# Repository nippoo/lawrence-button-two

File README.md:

# Lawrence Button Two

This repository contains the STL files, KiCad design and Gerber files, and Arduino code used in building the Lawrence Button Two. Unlike the first button (a custom STM32-based audio player) the electronics are a simpler, through-hole-only design.

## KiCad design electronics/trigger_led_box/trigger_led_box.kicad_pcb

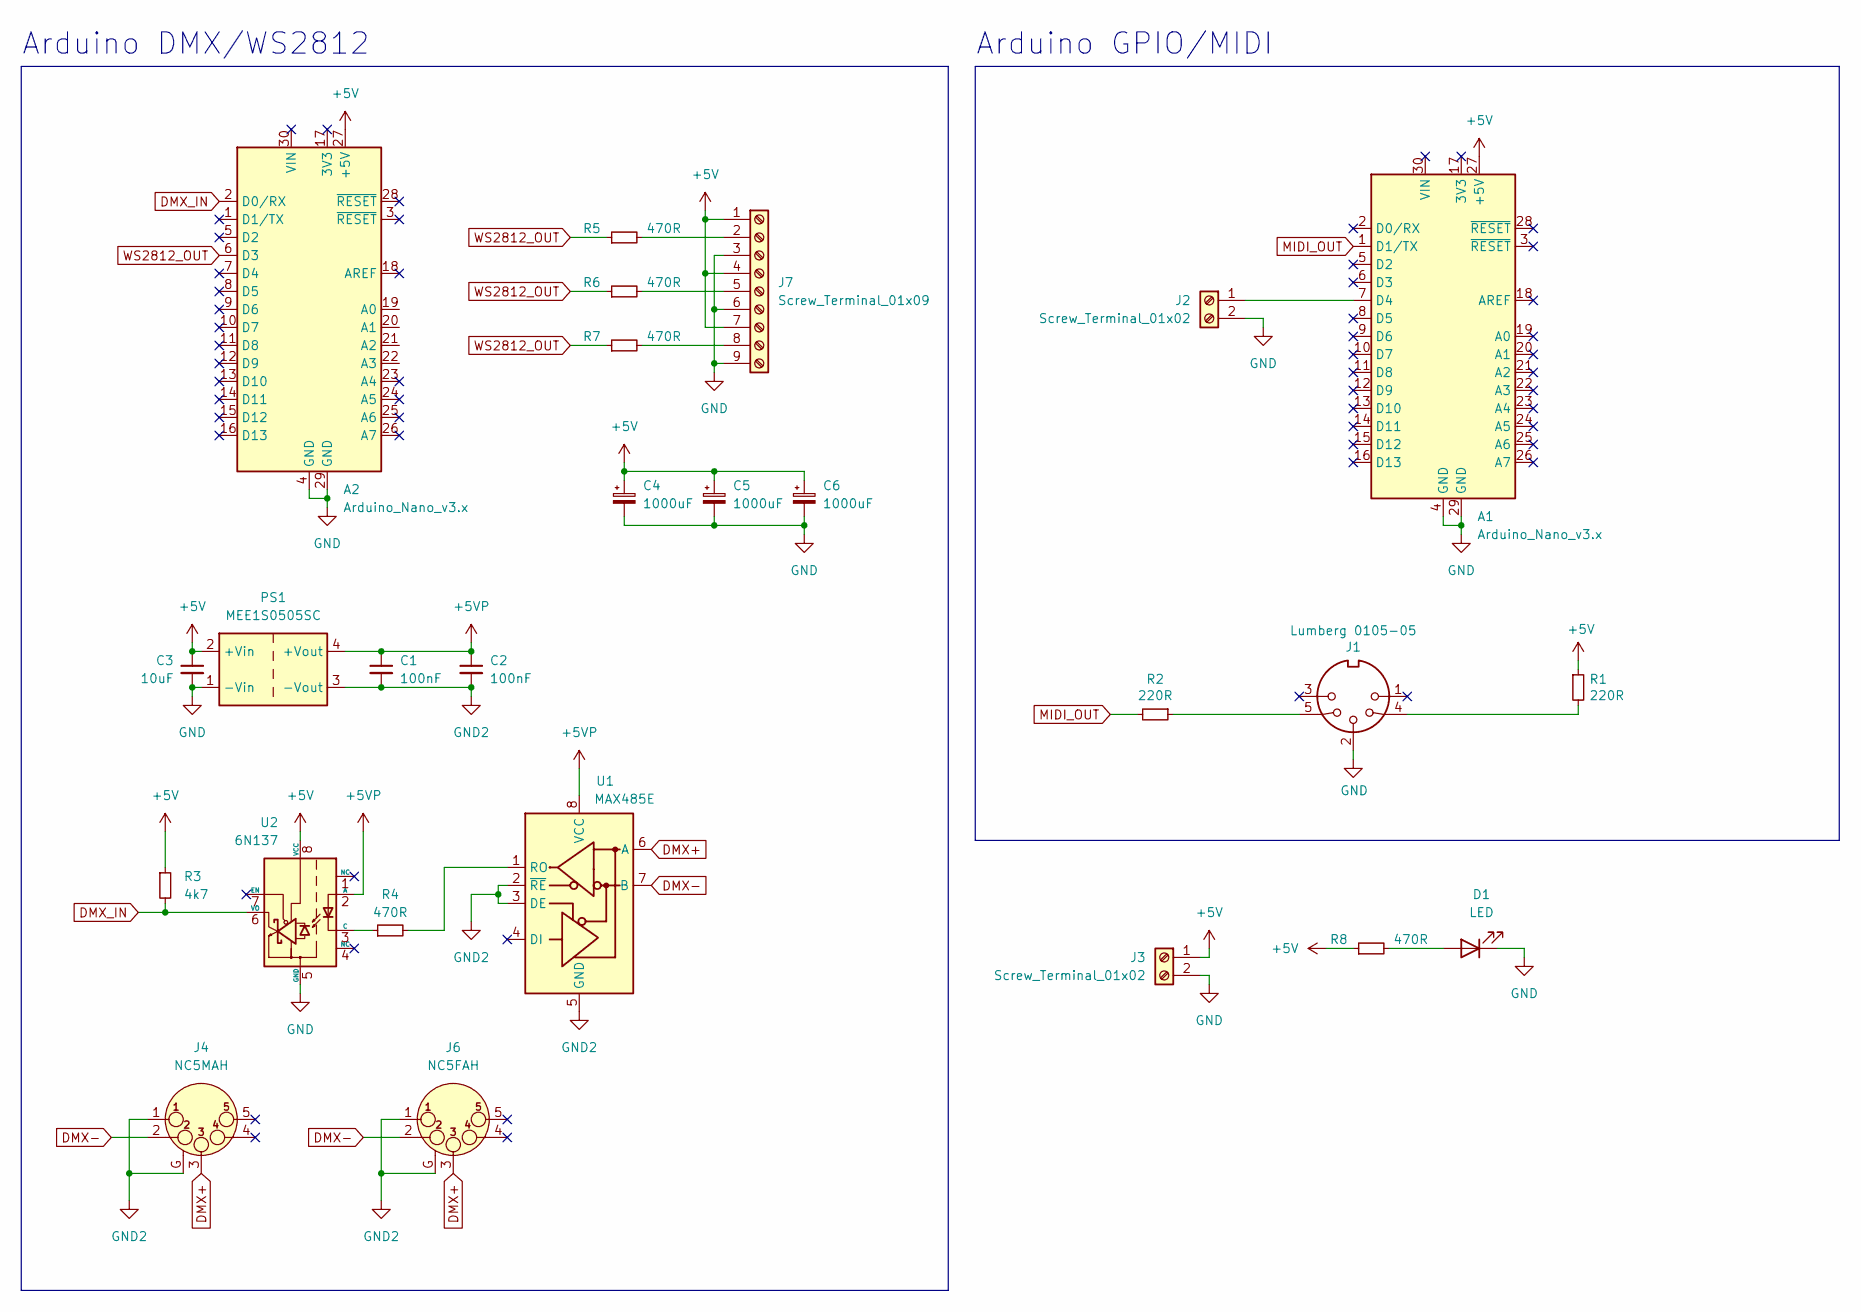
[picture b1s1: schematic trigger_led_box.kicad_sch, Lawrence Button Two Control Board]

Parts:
A1, A2: Arduino_Nano_v3.x; Arduino_Nano
C1, C2: 100nF; C_Rect_L7.0mm_W2.5mm_P5.00mm
C3: 10uF; C_Rect_L7.0mm_W2.5mm_P5.00mm
C4, C5, C6: 1000uF; CP_Radial_D10.0mm_P5.00mm
D1: LED; LED_D3.0mm_Horizontal_O1.27mm_Z10.0mm
J1: Lumberg 0105-05; Lumberg-0105-05
J2, J3: Screw_Terminal_01x02; TerminalBlock_Phoenix_PT-1,5-2-5.0-H_1x02_P5.00mm_Horizontal
J4: NC5MAH; Jack_XLR_Neutrik_NC5MAH_Horizontal
J6: NC5FAH; Jack_XLR_Neutrik_NC5FAH_Horizontal
J7: Screw_Terminal_01x09; TerminalBlock_Phoenix_PT-1,5-9-5.0-H_1x09_P5.00mm_Horizontal
PS1: MEE1S0505SC; Converter_DCDC_Murata_MEE1SxxxxSC_THT
R1, R2: 220R; R_Axial_DIN0207_L6.3mm_D2.5mm_P10.16mm_Horizontal; LCSC C22962
R3: 4k7; R_Axial_DIN0207_L6.3mm_D2.5mm_P10.16mm_Horizontal
R4, R5, R6, R7, R8: 470R; R_Axial_DIN0207_L6.3mm_D2.5mm_P10.16mm_Horizontal
U1: MAX485E; DIP-8_W7.62mm
U2: 6N137; DIP-8_W7.62mm

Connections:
+5V: A1.27 (+5V), A2.27 (+5V), C3.1, C4.1, C5.1, C6.1, J3.1, J7.1, J7.4, J7.7, PS1.2 (+Vin), R1.1, R3.1, R8.1, U2.8 (VCC)
+5VP: C1.1, C2.1, PS1.4 (+Vout), U1.8 (VCC), U2.2 (A)
DMX+: J4.3, J6.3, U1.6 (A)
DMX-: J4.2, J6.2, U1.7 (B)
DMX_IN: A2.2 (D0/RX), R3.2, U2.6 (VO)
GND: A1.4 (GND), A1.29 (GND), A2.4 (GND), A2.29 (GND), C3.2, C4.2, C5.2, C6.2, D1.1 (K), J1.2, J2.2, J3.2, J7.3, J7.6, J7.9, PS1.1 (-Vin), U2.5 (GND)
GND2: C1.2, C2.2, J4.1, J4.G, J6.1, J6.G, PS1.3 (-Vout), U1.2 (~RE), U1.3 (DE), U1.5 (GND)
MIDI_OUT: A1.1 (D1/TX), R2.2
unnamed: A1.7 (D4), J2.1
unnamed: D1.2 (A), R8.2
unnamed: J1.4, R1.2
unnamed: J1.5, R2.1
unnamed: J7.2, R5.2
unnamed: J7.5, R6.2
unnamed: J7.8, R7.2
unnamed: R4.2, U1.1 (RO)
unnamed: R4.1, U2.3 (C)
WS2812_OUT: A2.6 (D3), R5.1, R6.1, R7.1

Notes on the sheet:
Arduino GPIO/MIDI
Arduino DMX/WS2812

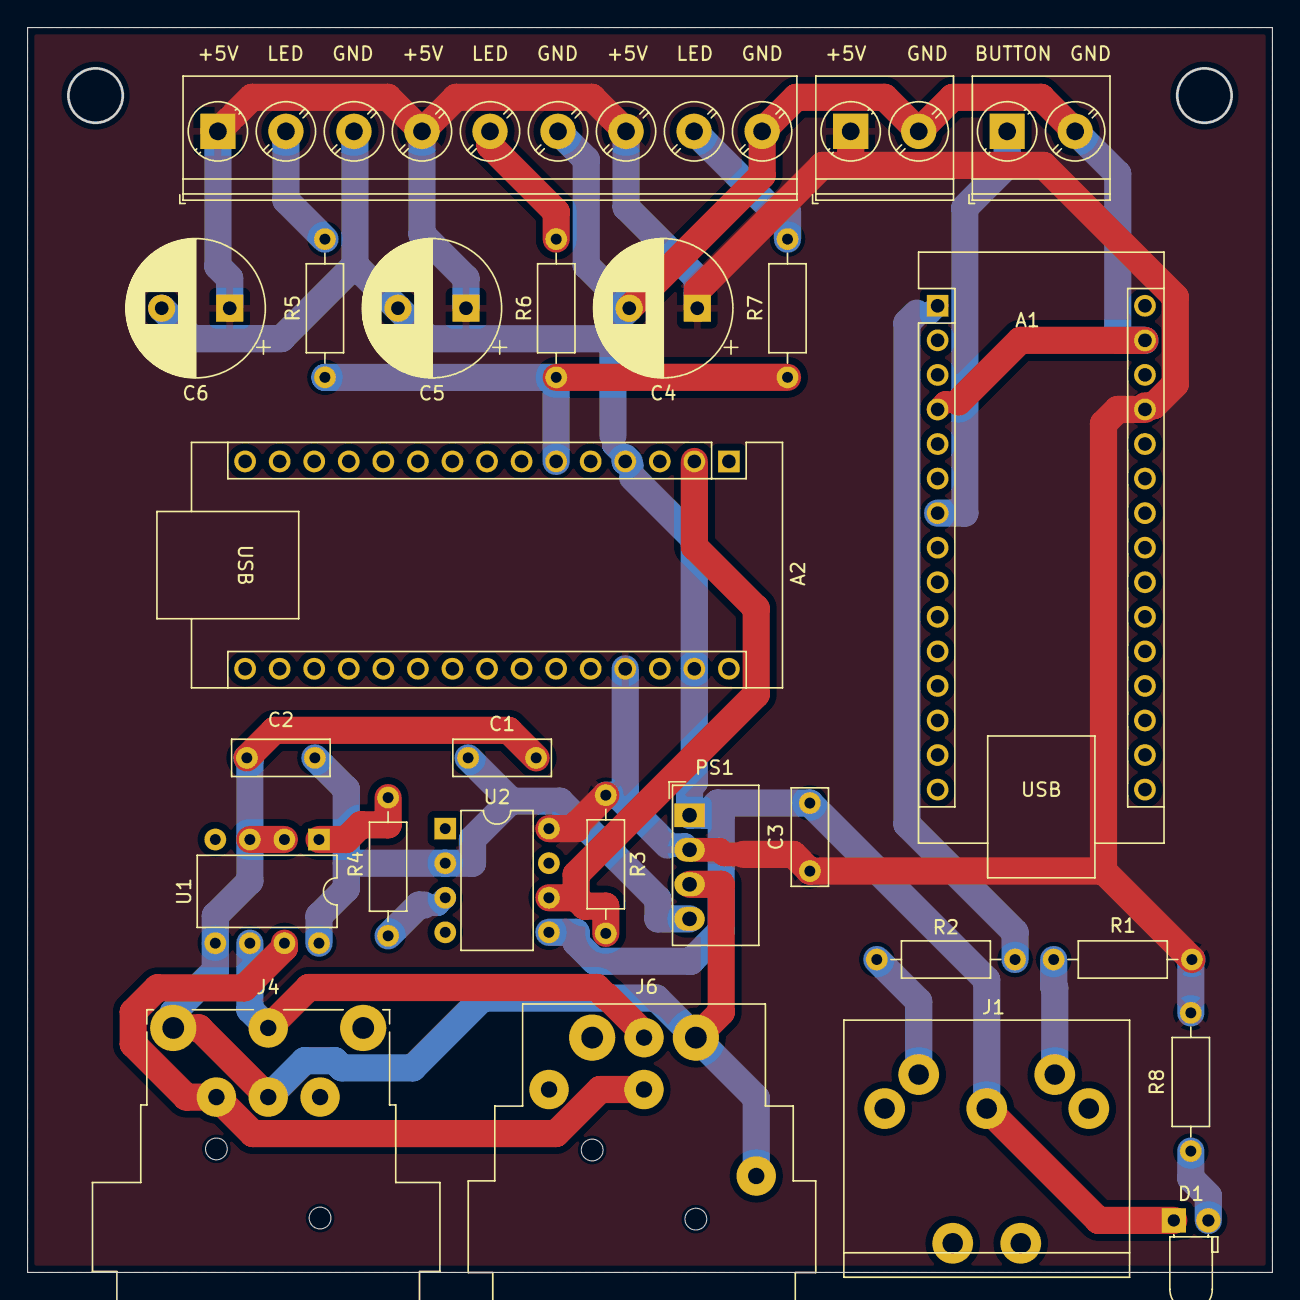
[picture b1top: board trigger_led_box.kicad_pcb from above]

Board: 2 copper layers, 91.4 x 91.4 mm, 26 parts (0 on the bottom side), 18 nets.

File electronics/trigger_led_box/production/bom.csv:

Designator,Footprint,Quantity,Value,LCSC Part #
"A1, A2",Arduino_Nano,2,Arduino_Nano_v3.x,
"C1, C2",C_Rect_L7.0mm_W2.5mm_P5.00mm,2,100nF,
C3,C_Rect_L7.0mm_W2.5mm_P5.00mm,1,10uF,
"C4, C5, C6",CP_Radial_D10.0mm_P5.00mm,3,1000uF,
D1,LED_D3.0mm_Horizontal_O1.27mm_Z10.0mm,1,LED,
J1,Lumberg-0105-05,1,Lumberg 0105-05,
"J2, J3","TerminalBlock_Phoenix_PT-1,5-2-5.0-H_1x02_P5.00mm_Horizontal",2,Screw_Terminal_01x02,
J4,Jack_XLR_Neutrik_NC5MAH_Horizontal,1,NC5MAH,
J6,Jack_XLR_Neutrik_NC5FAH_Horizontal,1,NC5FAH,
J7,"TerminalBlock_Phoenix_PT-1,5-9-5.0-H_1x09_P5.00mm_Horizontal",1,Screw_Terminal_01x09,
PS1,Converter_DCDC_Murata_MEE1SxxxxSC_THT,1,MEE1S0505SC,
"R1, R2",R_Axial_DIN0207_L6.3mm_D2.5mm_P10.16mm_Horizontal,2,220R,C22962
R3,R_Axial_DIN0207_L6.3mm_D2.5mm_P10.16mm_Horizontal,1,4k7,
"R4, R5, R6, R7, R8",R_Axial_DIN0207_L6.3mm_D2.5mm_P10.16mm_Horizontal,5,470R,
U1,DIP-8_W7.62mm,1,MAX485E,
U2,DIP-8_W7.62mm,1,6N137,

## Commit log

2024-07-12 v2 button production files
